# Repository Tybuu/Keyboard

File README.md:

# Tybeast Ones HE

 The Tybeast Ones HE is a split hall effect mechanical keyboard heavily
 inspired by the Corne. Written using the Rust Embassy framework.

## Loading Firmware

To load the firmware, you'll need to have [elf2uf2-rs](https://github.com/JoNil/elf2uf2-rs).
Once the KB2040 is in bootsel mode, you can use

`cargo run --release --bin <OPTION>`

where OPTION consists of either "left" or "right" depending on which
side you're loading for.

## Making Both Sides Connect

I for the life of me couldn't figure out how to solder a USB-C receptacle onto the PCB
so the firmware will have to use the HID protocol to communicate with
one another rather than using something like UART.
This can be done by using [Keyboard-Link](https://github.com/Tybuu/link).

## Components used in PCB

* Linear Hall Effect Sensors: AH49FNTR-G1
* Analog Multiplexers: CD74HC4051M96
* Dev Board: Adafruit KB2040

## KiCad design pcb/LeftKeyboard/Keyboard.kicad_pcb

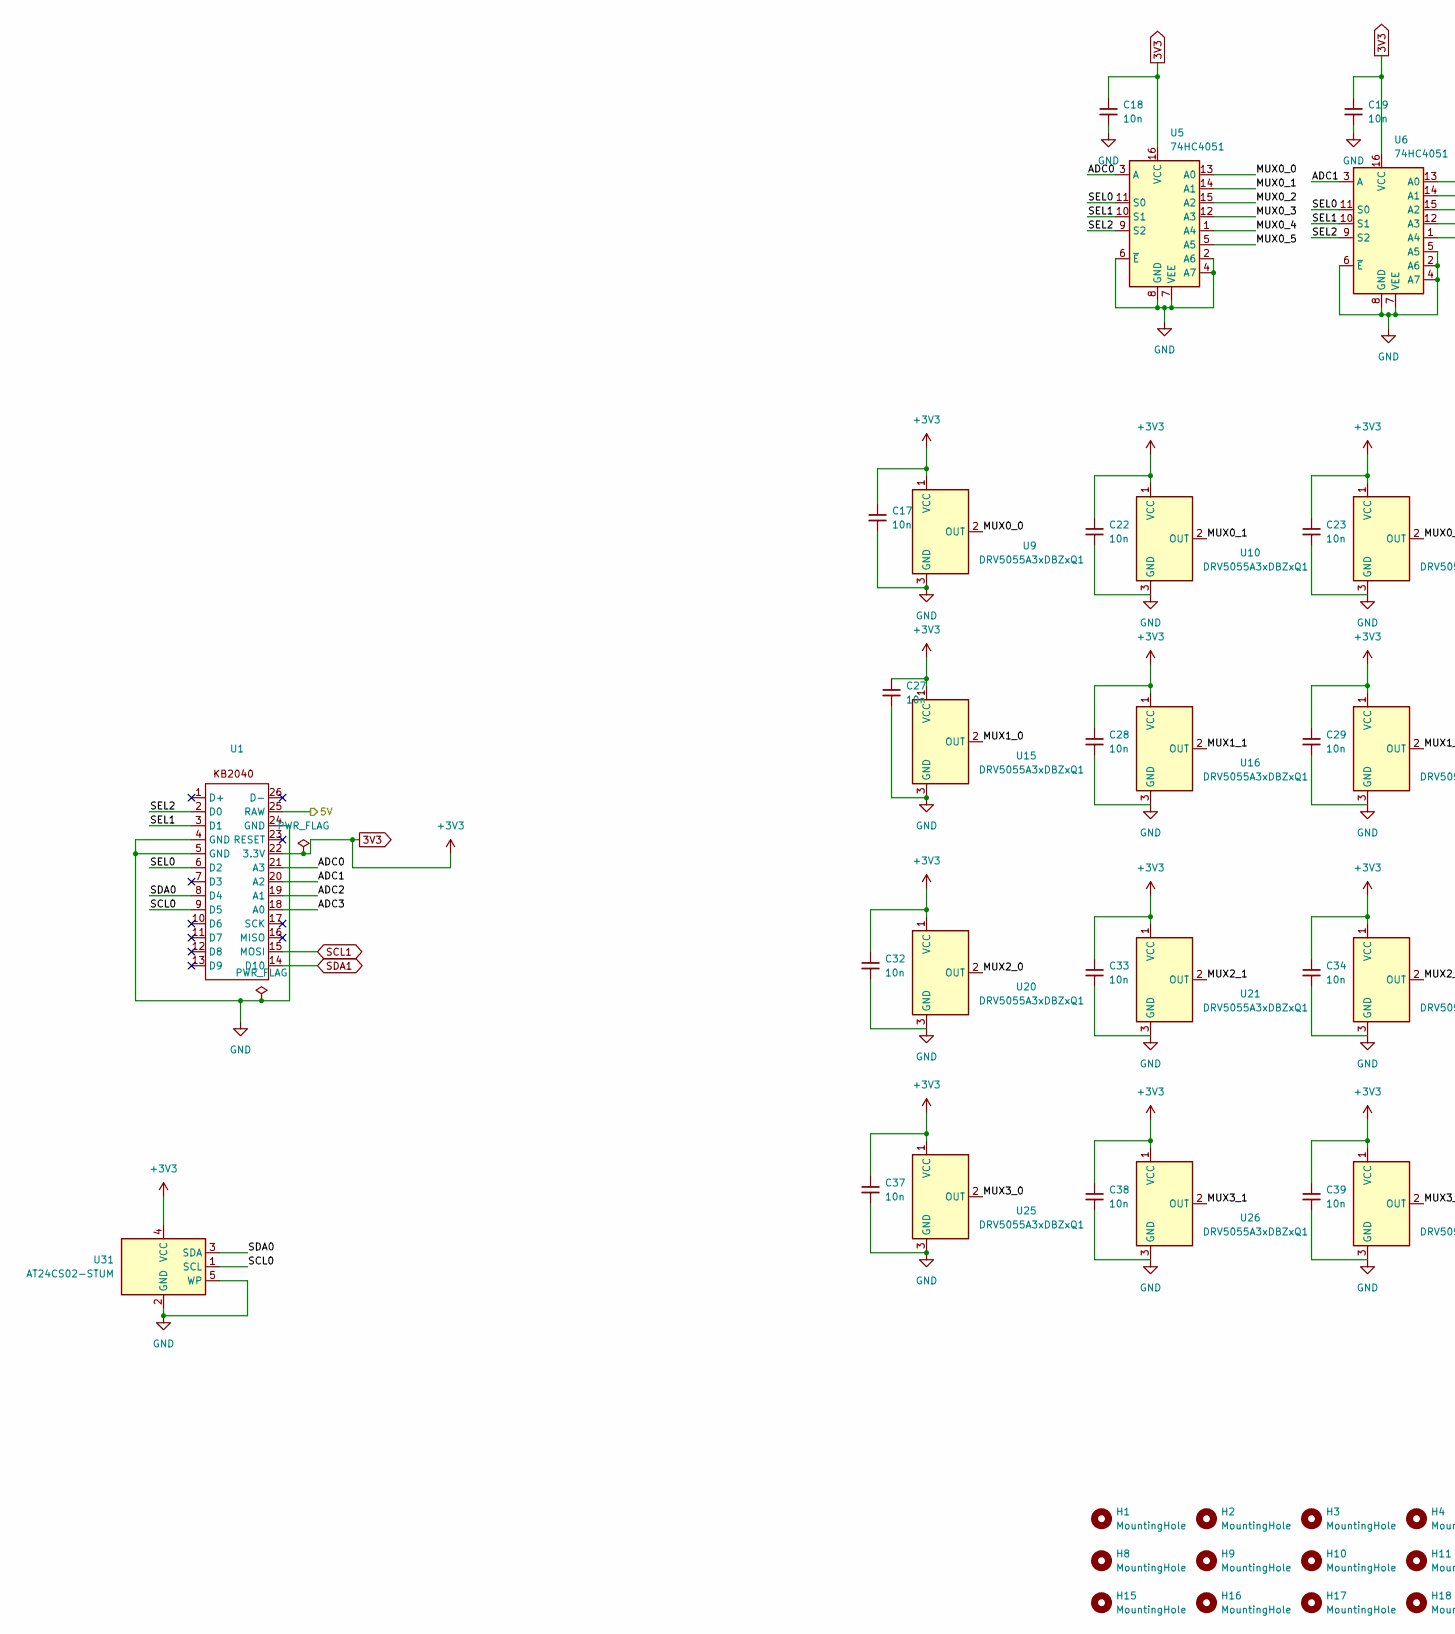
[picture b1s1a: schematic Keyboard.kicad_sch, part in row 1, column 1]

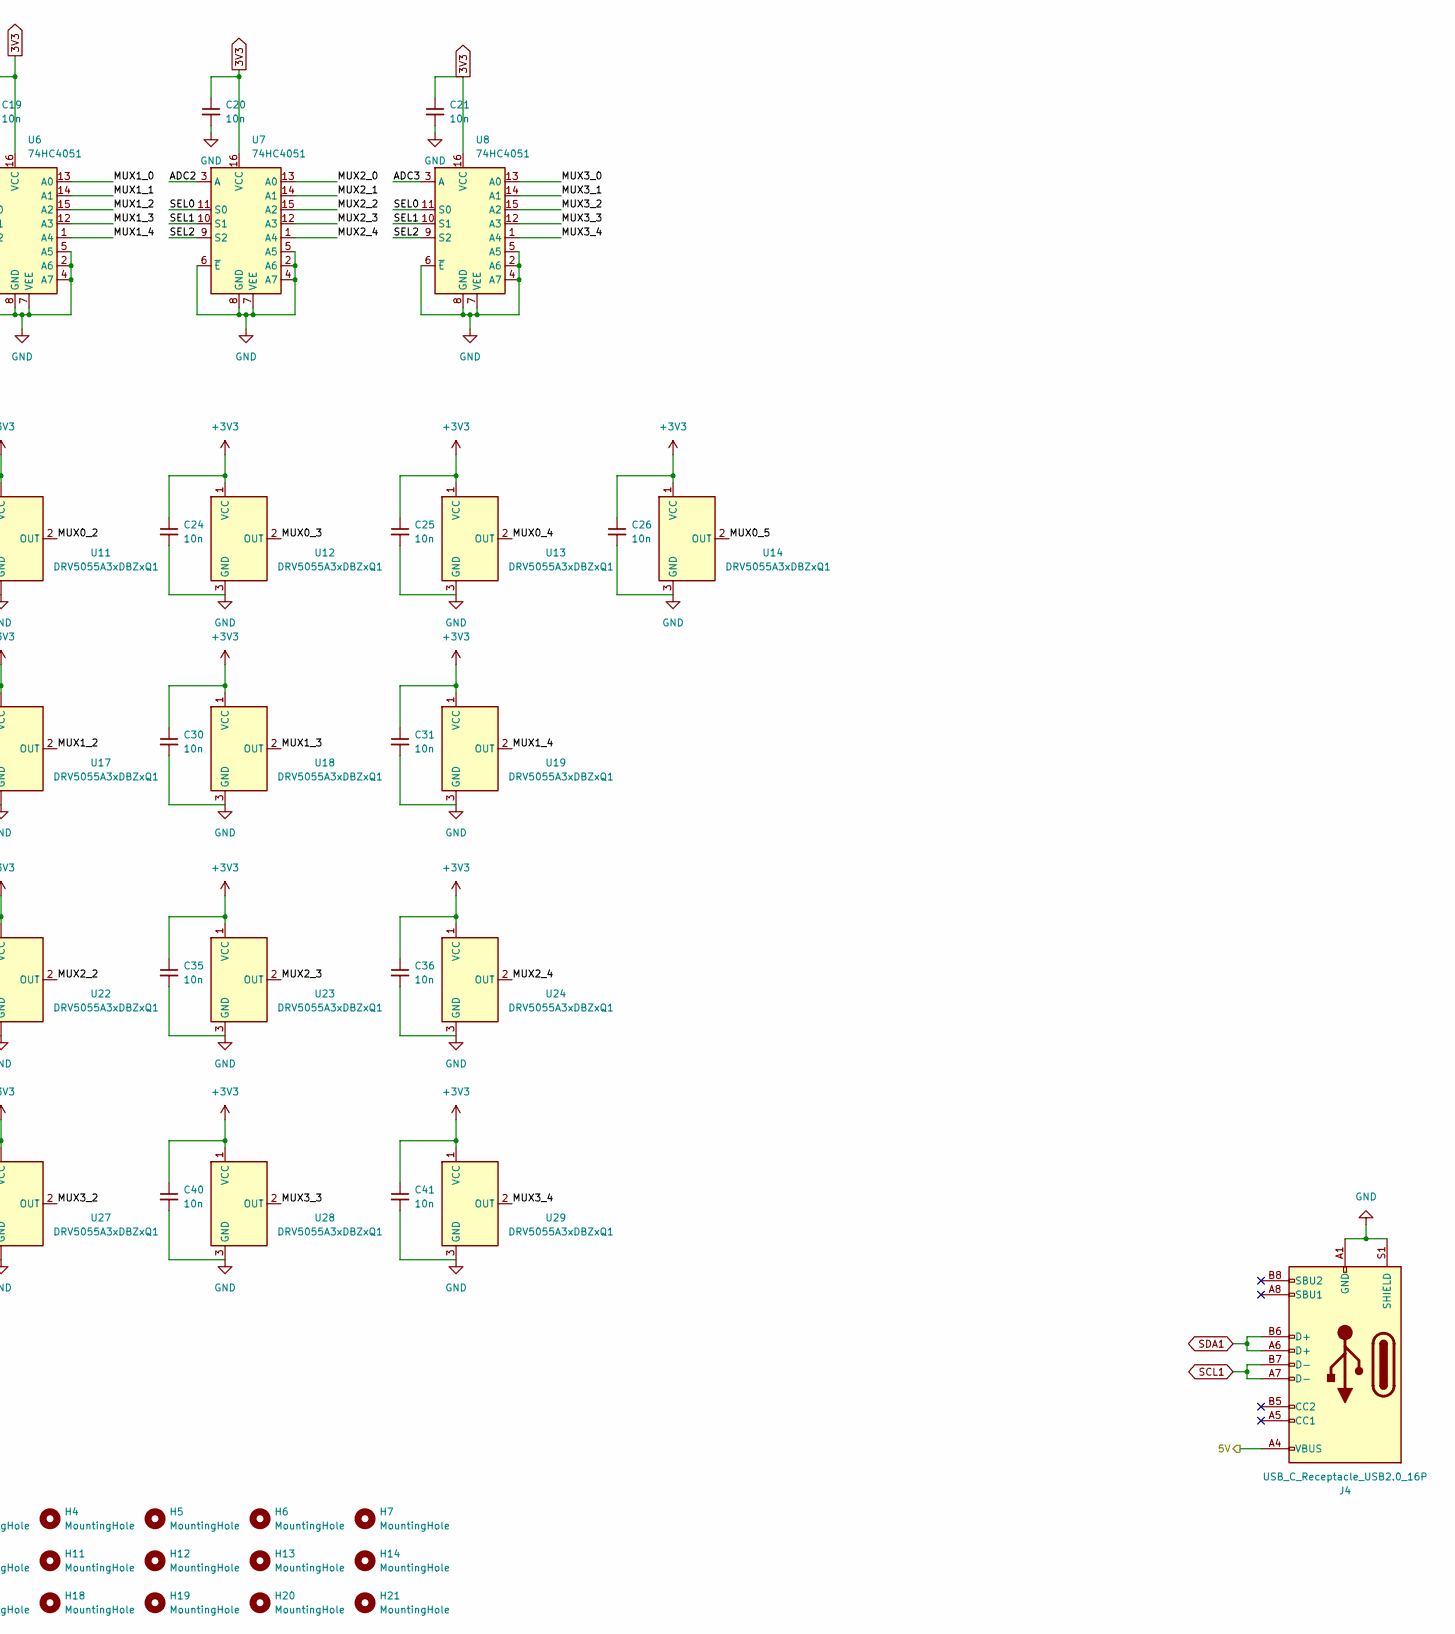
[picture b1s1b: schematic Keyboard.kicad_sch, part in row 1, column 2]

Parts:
C17, C18, C19, C20, C21, C22, C23, C24, C25, C26, C27, C28, C29, C30, C31, C32, C33, C34, C35, C36, C37, C38, C39, C40, C41: 10n; C_0402_1005Metric
H1, H2, H3, H4, H5, H6, H7, H8, H9, H10, H11, H12, H13, H14, H15, H16, H17, H18, H19, H20, H21: MountingHole; switch_holes
J4: USB_C_Receptacle_USB2.0_16P; USB_C_Receptacle_GCT_USB4105-xx-A_16P_TopMnt_Horizontal
U1: KB2040
U5, U6, U7, U8: 74HC4051; SOIC-16_3.9x9.9mm_P1.27mm
U9, U10, U11, U12, U13, U14, U15, U16, U17, U18, U19, U20, U21, U22, U23, U24, U25, U26, U27, U28, U29: DRV5055A3xDBZxQ1; SOT-23
U31: AT24CS02-STUM; SOT-23-5

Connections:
3V3: C17.1, C18.1, C19.1, C20.1, C21.1, C22.1, C23.1, C24.1, C25.1, C26.1, C27.1, C28.1, C29.1, C30.1, C31.1, C32.1, C33.1, C34.1, C35.1, C36.1, C37.1, C38.1, C39.1, C40.1, C41.1, U1.22 (3.3V), U5.16 (VCC), U6.16 (VCC), U7.16 (VCC), U8.16 (VCC), U9.1 (VCC), U10.1 (VCC), U11.1 (VCC), U12.1 (VCC), U13.1 (VCC), U14.1 (VCC), U15.1 (VCC), U16.1 (VCC), U17.1 (VCC), U18.1 (VCC), U19.1 (VCC), U20.1 (VCC), U21.1 (VCC), U22.1 (VCC), U23.1 (VCC), U24.1 (VCC), U25.1 (VCC), U26.1 (VCC), U27.1 (VCC), U28.1 (VCC), U29.1 (VCC), U31.4 (VCC)
/5V: J4.A4 (VBUS), J4.A9 (VBUS), J4.B4 (VBUS), J4.B9 (VBUS), U1.25 (RAW)
/ADC0: U1.21 (A3), U5.3 (A)
/ADC1: U1.20 (A2), U6.3 (A)
/ADC2: U1.19 (A1), U7.3 (A)
/ADC3: U1.18 (A0), U8.3 (A)
/MUX0_0: U5.13 (A0), U9.2 (OUT)
/MUX0_1: U5.14 (A1), U10.2 (OUT)
/MUX0_2: U5.15 (A2), U11.2 (OUT)
/MUX0_3: U5.12 (A3), U12.2 (OUT)
/MUX0_4: U5.1 (A4), U13.2 (OUT)
/MUX0_5: U5.5 (A5), U14.2 (OUT)
/MUX1_0: U6.13 (A0), U15.2 (OUT)
/MUX1_1: U6.14 (A1), U16.2 (OUT)
/MUX1_2: U6.15 (A2), U17.2 (OUT)
/MUX1_3: U6.12 (A3), U18.2 (OUT)
/MUX1_4: U6.1 (A4), U19.2 (OUT)
/MUX2_0: U7.13 (A0), U20.2 (OUT)
/MUX2_1: U7.14 (A1), U21.2 (OUT)
/MUX2_2: U7.15 (A2), U22.2 (OUT)
/MUX2_3: U7.12 (A3), U23.2 (OUT)
/MUX2_4: U7.1 (A4), U24.2 (OUT)
/MUX3_0: U8.13 (A0), U25.2 (OUT)
/MUX3_1: U8.14 (A1), U26.2 (OUT)
/MUX3_2: U8.15 (A2), U27.2 (OUT)
/MUX3_3: U8.12 (A3), U28.2 (OUT)
/MUX3_4: U8.1 (A4), U29.2 (OUT)
/SCL0: U1.9 (D5), U31.1 (SCL)
/SDA0: U1.8 (D4), U31.3 (SDA)
/SEL0: U1.6 (D2), U5.11 (S0), U6.11 (S0), U7.11 (S0), U8.11 (S0)
/SEL1: U1.3 (D1), U5.10 (S1), U6.10 (S1), U7.10 (S1), U8.10 (S1)
/SEL2: U1.2 (D0), U5.9 (S2), U6.9 (S2), U7.9 (S2), U8.9 (S2)
GND: C17.2, C18.2, C19.2, C20.2, C21.2, C22.2, C23.2, C24.2, C25.2, C26.2, C27.2, C28.2, C29.2, C30.2, C31.2, C32.2, C33.2, C34.2, C35.2, C36.2, C37.2, C38.2, C39.2, C40.2, C41.2, J4.A1 (GND), J4.A12 (GND), J4.B1 (GND), J4.B12 (GND), J4.S1 (SHIELD), U1.4 (GND), U1.5 (GND), U1.24 (GND), U5.2 (A6), U5.4 (A7), U5.6 (~E), U5.7 (VEE), U5.8 (GND), U6.2 (A6), U6.4 (A7), U6.5 (A5), U6.6 (~E), U6.7 (VEE), U6.8 (GND), U7.2 (A6), U7.4 (A7), U7.5 (A5), U7.6 (~E), U7.7 (VEE), U7.8 (GND), U8.2 (A6), U8.4 (A7), U8.5 (A5), U8.6 (~E), U8.7 (VEE), U8.8 (GND), U9.3 (GND), U10.3 (GND), U11.3 (GND), U12.3 (GND), U13.3 (GND), U14.3 (GND), U15.3 (GND), U16.3 (GND), U17.3 (GND), U18.3 (GND), U19.3 (GND), U20.3 (GND), U21.3 (GND), U22.3 (GND), U23.3 (GND), U24.3 (GND), U25.3 (GND), U26.3 (GND), U27.3 (GND), U28.3 (GND), U29.3 (GND), U31.2 (GND), U31.5 (WP)
SCL1: J4.A7 (D-), J4.B7 (D-), U1.15 (MOSI)
SDA1: J4.A6 (D+), J4.B6 (D+), U1.14 (D10)

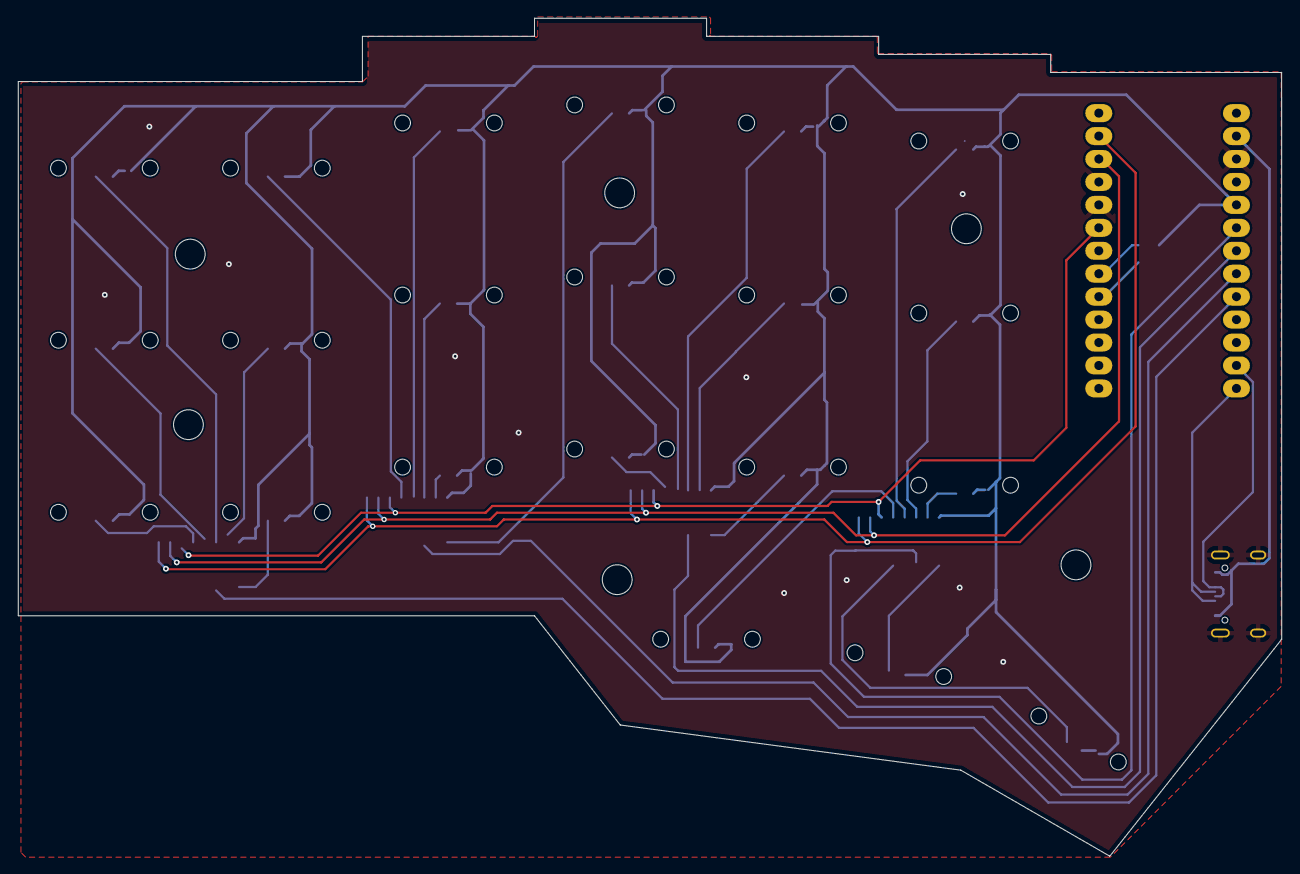
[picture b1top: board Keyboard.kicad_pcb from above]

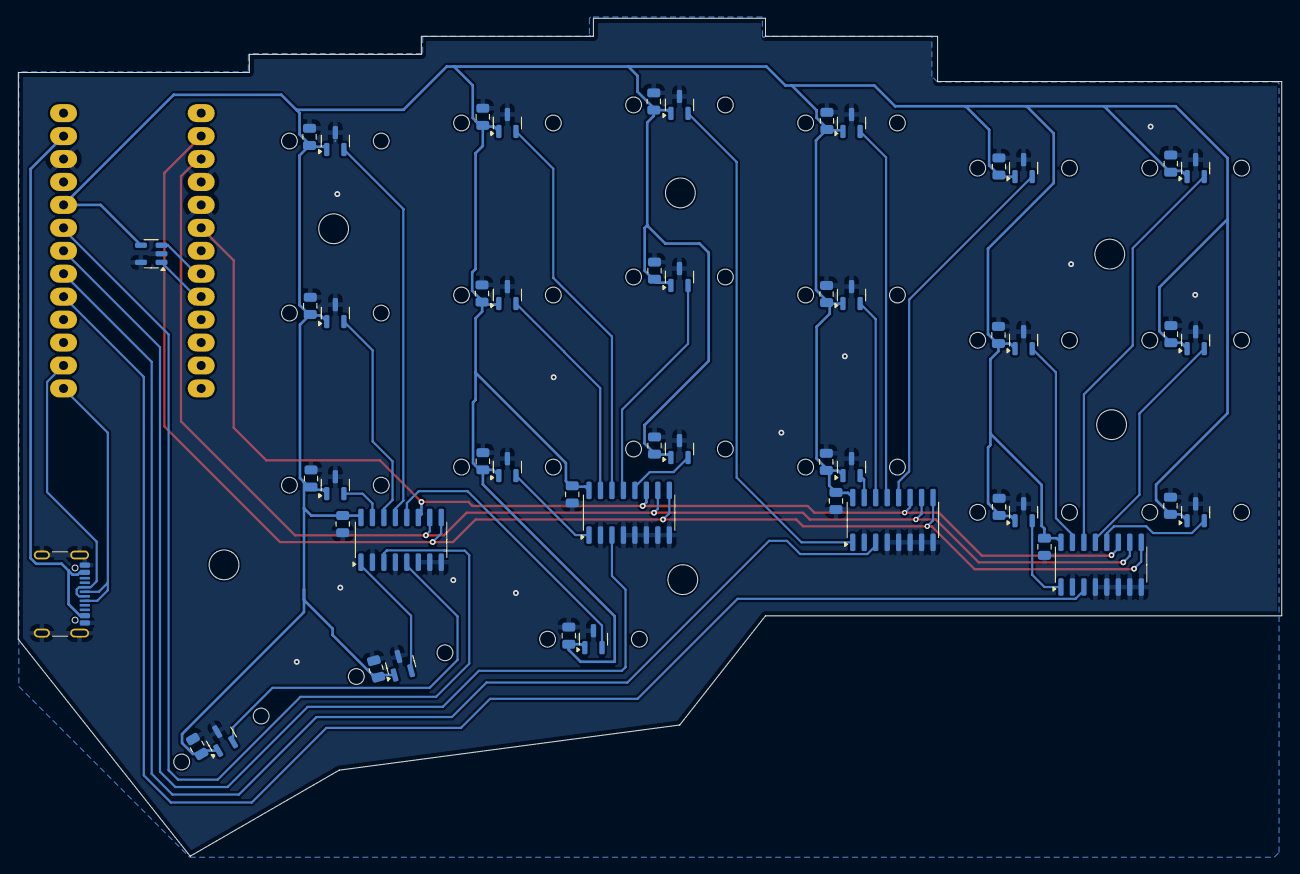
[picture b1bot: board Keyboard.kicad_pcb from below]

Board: 2 copper layers, 139.9 x 92.8 mm, 74 parts (73 on the bottom side), 35 nets.

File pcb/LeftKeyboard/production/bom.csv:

Designator,Footprint,Quantity,Value,LCSC Part #
"_6, _5, _4, _3, _2, ",,6,,
"C17, C18, C19, C20, C21, C22, C23, C24, C25, C26, C27, C28, C29, C30, C31, C32, C33, C34, C35, C36, C37, C38, C39, C40, C41",0805,25,10n,
J4,USB_C_Receptacle_GCT_USB4105-xx-A_16P_TopMnt_Horizontal,1,USB_C_Receptacle_USB2.0_16P,
U1,KB2040,1,~,
"U10, U11, U12, U13, U14, U15, U16, U17, U18, U19, U20, U21, U22, U23, U24, U25, U26, U27, U28, U29, U9",SOT-23,21,DRV5055A3xDBZxQ1,
U31,SOT-23-5,1,AT24CS02-STUM,
"U5, U6, U7, U8",SOIC-16_3.9x9.9mm_P1.27mm,4,74HC4051,

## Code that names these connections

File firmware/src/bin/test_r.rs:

//! This example test the RP Pico on board LED.
//!
//! It does not work with the RP Pico W board. See wifi_blinky.rs.

#![no_std]
#![no_main]

use core::sync::atomic::{AtomicBool, Ordering};

use defmt::info;
use embassy_executor::Spawner;
use embassy_futures::join::join;
use embassy_rp::adc::{self, Adc, Channel, Config as AdcConfig};
use embassy_rp::gpio::{Pin, Pull};
use embassy_rp::peripherals::USB;
use embassy_rp::{bind_interrupts, gpio, peripherals, usb};
use embassy_sync::blocking_mutex::raw::CriticalSectionRawMutex;
use embassy_sync::mutex::Mutex;
use embassy_time::Timer;
use keyboard::descriptor::{BufferReport, KeyboardReportNKRO, MouseReport, SlaveKeyReport};
use keyboard::keys::Keys;

use embassy_rp::usb::Driver;
use embassy_usb::class::hid::{HidReaderWriter, HidWriter, State};
use embassy_usb::{Builder, Config, Handler};
use gpio::{Level, Output};
use keyboard::report::Report;
use usbd_hid::descriptor::SerializedDescriptor;
use {defmt_rtt as _, panic_probe as _};

bind_interrupts!(struct Irqs {
    USBCTRL_IRQ => usb::InterruptHandler<peripherals::USB>;
    ADC_IRQ_FIFO => adc::InterruptHandler;
});

static MUX: Mutex<CriticalSectionRawMutex, [u8; 3]> = Mutex::new([0u8; 3]);

const SCROLL_TIME: u64 = 500;
const MOUSE_POINTER_TIME: u64 = 10;

const NUM_KEYS: usize = 21;

#[embassy_executor::task]
async fn logger_task(driver: Driver<'static, USB>) {
    embassy_usb_logger::run!(1024, log::LevelFilter::Info, driver);
}

#[embassy_executor::main]
async fn main(_spawner: Spawner) {
    info!("Device Started!");
    let p = embassy_rp::init(Default::default());
    // Create the driver, from the HAL.
    let driver = Driver::new(p.USB, Irqs);

    // Sel Pins
    let mut sel0 = Output::new(p.PIN_0, Level::Low);
    let mut sel1 = Output::new(p.PIN_1, Level::Low);
    let mut sel2 = Output::new(p.PIN_2, Level::Low);

    // Adc
    let mut adc = Adc::new(p.ADC, Irqs, AdcConfig::default());
    let mut a3 = Channel::new_pin(p.PIN_26, Pull::None);
    let mut a2 = Channel::new_pin(p.PIN_27, Pull::None);
    let mut a1 = Channel::new_pin(p.PIN_28, Pull::None);
    let mut a0 = Channel::new_pin(p.PIN_29, Pull::None);

    let mut order: [usize; NUM_KEYS] = [
        4, 5, 18, 2, 14, 7, 0, 9, 1, 6, 11, 3, 12, 17, 13, 10, 19, 15, 20, 16, 8,
    ];
    find_order(&mut order);

    let mut keys = Keys::<NUM_KEYS>::default();

    let mut report = SlaveKeyReport::default();

    _spawner.spawn(logger_task(driver)).unwrap();
    // Main keyboard loop
    loop {
        let mut pos = 0;
        for i in order {
            let chan = pos % 4;
            if chan == 0 {
                change_sel(&mut sel0, &mut sel1, &mut sel2, pos / 4);
                Timer::after_micros(1).await;
            }
            match chan {
                0 => keys.update_buf(i, 4095 - adc.read(&mut a0).await.unwrap()),
                1 => keys.update_buf(i, 4095 - adc.read(&mut a1).await.unwrap()),
                2 => keys.update_buf(i, 4095 - adc.read(&mut a2).await.unwrap()),
                3 => keys.update_buf(i, 4095 - adc.read(&mut a3).await.unwrap()),
                _ => {}
            }
            pos += 1;
        }
        let key_report = report.generate_report(&mut keys);
        log::info!(
            "[{}, {}, {}, {}, {}, {}",
            keys.get_buf(0),
            keys.get_buf(1),
            keys.get_buf(2),
            keys.get_buf(3),
            keys.get_buf(4),
            keys.get_buf(5),
        );

        log::info!(
            "{}, {}, {}, {}, {}, {}",
            keys.get_buf(6),
            keys.get_buf(7),
            keys.get_buf(8),
            keys.get_buf(9),
            keys.get_buf(10),
            keys.get_buf(11),
        );

        log::info!(
            "{}, {}, {}, {}, {}, {}",
            keys.get_buf(12),
            keys.get_buf(13),
            keys.get_buf(14),
            keys.get_buf(15),
            keys.get_buf(16),
            keys.get_buf(17),
        );

        log::info!(
            "{}, {}, {}",
            keys.get_buf(18),
            keys.get_buf(19),
            keys.get_buf(20),
        );
        Timer::after_millis(20).await;
    }
}

struct MyDeviceHandler {
    configured: AtomicBool,
}

impl MyDeviceHandler {
    fn new() -> Self {
        MyDeviceHandler {
            configured: AtomicBool::new(false),
        }
    }
}

impl Handler for MyDeviceHandler {
    fn enabled(&mut self, enabled: bool) {
        self.configured.store(false, Ordering::Relaxed);
        if enabled {
            info!("Device enabled");
        } else {
            info!("Device disabled");
        }
    }

    fn reset(&mut self) {
        self.configured.store(false, Ordering::Relaxed);
        info!("Bus reset, the Vbus current limit is 100mA");
    }

    fn addressed(&mut self, addr: u8) {
        self.configured.store(false, Ordering::Relaxed);
        info!("USB address set to: {}", addr);
    }

    fn configured(&mut self, configured: bool) {
        self.configured.store(configured, Ordering::Relaxed);
        if configured {
            info!(
                "Device configured, it may now draw up to the configured current limit from Vbus."
            )
        } else {
            info!("Device is no longer configured, the Vbus current limit is 100mA.");
        }
    }
}

fn find_order(ary: &mut [usize]) {
    let mut new_ary = [0usize; 21 as usize];
    for i in 0..ary.len() {
        for j in 0..ary.len() {
            if ary[j as usize] == i {
                new_ary[i as usize] = j;
            }
        }
    }
    ary.copy_from_slice(&new_ary);
}

fn change_sel<P0: Pin, P1: Pin, P2: Pin>(
    sel0: &mut Output<P0>,
    sel1: &mut Output<P1>,
    sel2: &mut Output<P2>,
    num: u8,
) {
    match num {
        0 => {
            sel0.set_low();
            sel1.set_low();
            sel2.set_low();
        }
        1 => {
            sel0.set_high();
            sel1.set_low();
            sel2.set_low();
        }
        2 => {
            sel0.set_low();
            sel1.set_high();
            sel2.set_low();
        }
        3 => {
            sel0.set_high();
            sel1.set_high();
            sel2.set_low();
        }
        4 => {
            sel0.set_low();
            sel1.set_low();
            sel2.set_high();
        }
        5 => {
            sel0.set_high();
            sel1.set_low();
            sel2.set_high();
        }
        _ => {
            sel0.set_low();
            sel1.set_low();
            sel2.set_low();
        }
    }
}

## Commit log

2024-08-21 Switched to Embassy framework
2024-08-22 Added right keyboard code
2024-08-27 Added pcb files and readme
2024-09-08 Added first implementation of mod taps
2024-11-24 added ability to change config on the fly
2024-12-24 changed key config
2025-03-24 config update
2025-04-16 added nix flakes
2025-04-22 added one shot
2025-07-04 changed config
